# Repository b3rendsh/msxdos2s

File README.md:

# msxdos2s
- Enhanced MSX DOS 2.2 / 2.31 in a 32K ROM package
- Enhanced MSX DOS 1
- Optimized BEER, MALT and SODA IDE interface drivers
- Disk hardware interface designs
- MSX JIO client

## Introduction
This repository contains a re-composition of the MSX DOS 2 disk ROM that can be used as a 32K ROM without a ROM mapper (or 16K ROM for the BEER interface) and includes enhancements for large disks. 

There is also a version of MSX DOS 1 which contains enhancements that are based on the 16K BEER IDE disk ROM that SOLiD created.

And thirdly it includes disk drivers for MSX-DOS 1 and 2 that can be used with the BEER, MALT, SODA and JIO disk interfaces.

All functions of MSX DOS 1 and MSX DOS 2 as originally distributed by ASCII have been retained and should work 100% the same except for the changes that are mentioned below.
The disk ROM works with the original msxdos(2).sys and command(2).com loaded from disk media such as a floppy or IDE disk / compact flash card. 
The disk ROM also works if there are other disk interfaces in the machine and it is compliant with the MSX standards to determine which disk interface will be the master.

## Enhanced MSX DOS IDE disk system

[BEER and SODA ROM package](https://github.com/b3rendsh/msxdos2s/blob/main/rom/beer_and_soda.zip)  
[Source code](dev-32k/)  

Following DOS and driver enhancements are included:
1. Support for large disks with a standard Master Boot Record.
2. Maximum of 4 primary partitions and/or 1 or more extended partitions.
3. Maximum of 8 partitions.
4. Support for FAT16 file systems.
5. Boot drive selection (boot menu).
6. Support for standard DOS 2 or Nextor partitions and disk format.

#### MSX DOS 2 changes
1. Added support for [FAT16 partitions](docs/FAT16%20partitions.txt)
2. Kanji and ROM check ("call dos2memchk" in BASIC) are removed to reduce the size of the ROM.
3. The ROM mapper code is removed and all the code is consolidated in a contiguous 32K ROM space.
4. If the turbo R specific changes are included with the DOS v2.31 option then the ROM still works on older machines.

#### MSX DOS 1 changes
1. Added support for [FAT16 partitions](docs/FAT16%20partitions.txt)
2. Added FAT swapper from SOLiD to support partitions larger than 16MB.

#### Universal IDE driver
The IDE driver is split into a common DOS layer and a low level disk interface layer. It currently supports the BEER-202, BEER-232 and SODA disk interface hardware. If the hardware is not detected then a dummy driver is used.
1. The code is optimized to increase the data transfer rate.
2. Detection of hardware and I/O ports for the MALT and SODA interfaces.
3. Includes support for extended partitions and up to 8 drives.
4. Only one master IDE disk is supported. No master/slave or ATAPI (CDROM) drives. The SODA interface works with CF cards only.
5. Optional execution of boot code in the MBR, in addition or as a replacement for the boot menu.

## Disk interfaces 
**BEER-202 IDE interface**  
This is the original BEER interface, there are several designs with small variations that you can build yourself.  
The [16K MSX-DOS 1 disk ROM](rom/) and [16K MSX-DOS 2 disk ROM](dev-16k/) can be used with this interface.  
  
[**BEER-232 IDE interface**](hardware/beer-232/)  
The BEER-232 cartridge is derived from the BEER-202 and supports 2x 32K disk ROM instead of a single 16K ROM.

[**MALT IDE interface**](hardware/malt/)  
The MALT cartridge is a more robust alternative for the classic BEER IDE that also uses a 8255 PPI chip.

[**SODA IDE interface**](https://github.com/Danjovic/Soda-IDE)  
The SODA IDE cartridge design is based on a RCBus Compact Flash module. Danjovic adapted this design for MSX and made the PCB layout.  
  
[**MSX JIO**](https://github.com/louthrax/MSXJIO)  
Remote serial disk solution from Louthrax. It consists of a disk image server on a PC or android phone, a MSX client and a serial connection over the MSX joystick (gpio) port 2 using a ftdi cable or bluetooth adapter. 

[**MSX JIO CART**](https://github.com/herraa1/msx-jio-cart-v1)  
MSX JIO cartridge from Herraa1. Software based serial communnications like MSXJIO but without using joystick port 2.

[**TASTE program**](https://github.com/b3rendsh/cxland/tree/main/apps/taste)  
IDE disk info and test utility for MSX and RomWBW compatible computers. Works with BEER, MALT and SODA interfaces.

## Older versions

#### 32K MSX DOS 2.2
[ROM binaries](rom/)  
[Source files](mod-32k/)  
The main changes compared to ASCII's MSXDOS 2.2 are that this ROM works without a ROM mapper and doesn't contain Kanji support. Only the original dummy disk driver from ASCII is included, no OEM disk interface driver. Also the enhancements that are mentioned above are not included. 

#### 16K BEER-IDE 2.0
[BEER-IDE 2.0 ROM](https://github.com/b3rendsh/msxdos2s/blob/main/rom/BEER20_DISK.ROM)  
[Source files](mod-beer20/)  
The main improvement compared to the 1.9 driver is that it will work with other disk systems in the machine that have higher DOS versions e.g. a SUNRISE IDE with MSX DOS 2.2 or Nextor. Some other nasty bugs have been fixed. In the source code all the differences between v1.9 and v2.0 are marked and commented in detail.

To use MiSiX DOS use the 2.0 ROM or compile with 1.9 compatibility options, newer ROM versions don't work with MiSiX.

## Contributions
Although contributions of all kinds are welcome, I have no intention to add any more features or modify the DOS kernel in this repository.

Please create an issue if you want to report a bug or have any requests or suggestions. Pull requests from forks are currently not supported.

## License
Most of the sources are a re-composition of the creative work of ASCII and others. They are shared here for educational and non commercial purposes only. It is believed that these works are being used in accordance with the intentions and/or licensing of their creators.

The Creative Commons license terms apply to all custom source code, drivers and binaries.

The material is provided freely and "as it is" in the hope that it will be useful, but without any warranty of any kind, either expressed or implied. Use at own risk!

## References
MSX system sources:  
https://sourceforge.net/projects/msxsyssrc/  
  
MSX DOS 2:  
https://www.msx.org/wiki/MSX-DOS_2  

Other:
- MSX Technical Data Book for MSX-DOS 1
- MSX DOS 2 System Specification 1986-11-26
- Nextor 2.1 Driver Development Guide (github)
- Microsoft FAT Specification (August 30 2005)
- IDE ata3 specification (Revision 6, 26 October 1995)
- Intel 8255A PPI data sheet (August 1991)

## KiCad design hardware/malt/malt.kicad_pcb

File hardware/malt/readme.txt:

MALT IDE
========

MSX 8255 PPI IDE board that is based on the Eurocard Bus DiskIO V3 PPIDE design
for retrocomputers.

It uses the same 8255 PPI chip as the MSX BEER interface but the IDE control
signals are implemented in a more robust way.

Note: see patch document for the pcb version 1.1, these changes will be included 
in the upcoming pcb version 1.2

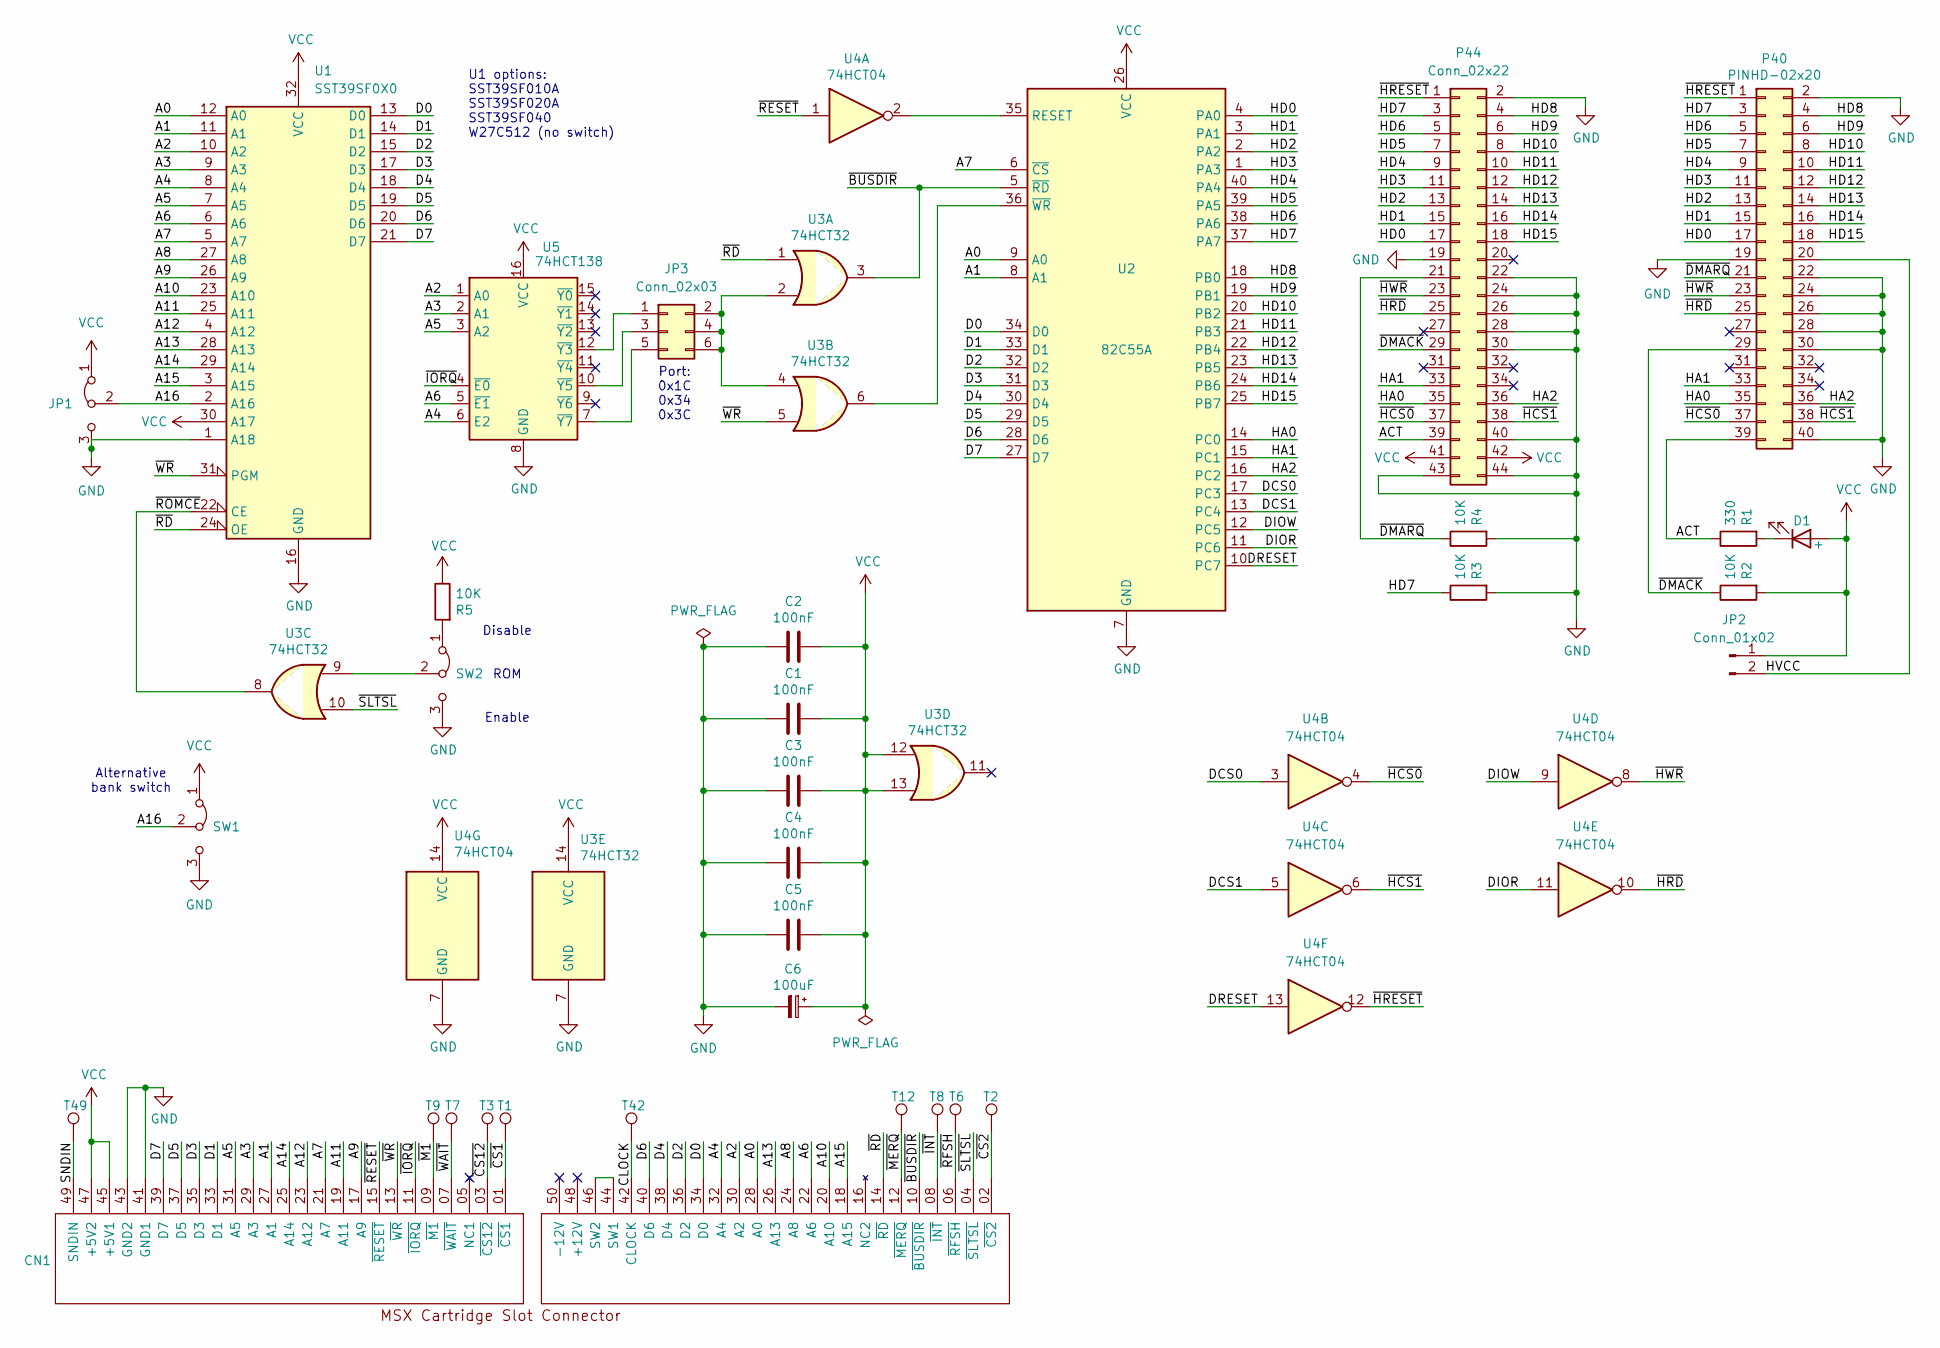
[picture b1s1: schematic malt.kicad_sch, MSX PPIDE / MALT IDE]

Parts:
C1, C2, C3, C4, C5: 100nF; C_Disc_D4.7mm_W2.5mm_P5.00mm
C6: 100uF; CP_lying
CN1: MSX_SLOT_CON; Cart_Konami
D1: +; LED_D3.0mm
JP1: PIN_1x3; PinHeader_1x03_P2.54mm_Vertical
JP2: Conn_01x02; PinHeader_1x02_P2.54mm_Vertical
JP3: Conn_02x03; PinHeader_2x03_P2.54mm_Vertical
P40: PINHD-02x20; PinHeader_2x20_P2.54mm_Horizontal
P44: Conn_02x22; PinHeader_2x22_P2.00mm_Vertical
R1: 330; R_Axial_DIN0204_L3.6mm_D1.6mm_P7.62mm_Horizontal
R2, R3, R4, R5: 10K; R_Axial_DIN0204_L3.6mm_D1.6mm_P7.62mm_Horizontal
SW1, SW2: PIN_1x3; SW_Slide_SPDT_Angled_CK_OS102011MA1Q
T1, T2, T3, T6, T7, T8, T9, T12, T42, T49: TestPoint; SolderWirePad_1x01_SMD_1x2mm
U1: SST39SF0X0; DIP-32_W15.24mm_Socket
U2: 82C55A; DIP-40_W15.24mm
U3: 74HCT32; DIP-14_W7.62mm
U4: 74HCT04; DIP-14_W7.62mm
U5: 74HCT138; DIP-16_W7.62mm

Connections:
/A0: CN1.28 (A0), U1.12 (A0), U2.9 (A0)
/A1: CN1.27 (A1), U1.11 (A1), U2.8 (A1)
/A2: CN1.30 (A2), U1.10 (A2), U5.1 (A0)
/A3: CN1.29 (A3), U1.9 (A3), U5.2 (A1)
/A4: CN1.32 (A4), U1.8 (A4), U5.6 (E2)
/A5: CN1.31 (A5), U1.7 (A5), U5.3 (A2)
/A6: CN1.22 (A6), U1.6 (A6), U5.5 (~E1)
/A7: CN1.21 (A7), U1.5 (A7), U2.6 (~CS)
/A8: CN1.24 (A8), U1.27 (A8)
/A9: CN1.17 (A9), U1.26 (A9)
/A10: CN1.20 (A10), U1.23 (A10)
/A11: CN1.19 (A11), U1.25 (A11)
/A12: CN1.23 (A12), U1.4 (A12)
/A13: CN1.26 (A13), U1.28 (A13)
/A14: CN1.25 (A14), U1.29 (A14)
/A15: CN1.18 (A15), U1.3 (A15)
/A16: JP1.2 (C), SW1.2 (C), U1.2 (A16)
/ACT: P40.39, P44.39, R1.1
/CLOCK: CN1.42 (CLOCK), T42.1
/D0: CN1.34 (D0), U1.13 (D0), U2.34 (D0)
/D1: CN1.33 (D1), U1.14 (D1), U2.33 (D1)
/D2: CN1.36 (D2), U1.15 (D2), U2.32 (D2)
/D3: CN1.35 (D3), U1.17 (D3), U2.31 (D3)
/D4: CN1.38 (D4), U1.18 (D4), U2.30 (D4)
/D5: CN1.37 (D5), U1.19 (D5), U2.29 (D5)
/D6: CN1.40 (D6), U1.20 (D6), U2.28 (D6)
/D7: CN1.39 (D7), U1.21 (D7), U2.27 (D7)
/DCS0: U2.17 (PC3), U4.3
/DCS1: U2.13 (PC4), U4.5
/DIOR: U2.11 (PC6), U4.11
/DIOW: U2.12 (PC5), U4.9
/DRESET: U2.10 (PC7), U4.13
/HA0: P40.35, P44.35, U2.14 (PC0)
/HA1: P40.33, P44.33, U2.15 (PC1)
/HA2: P40.36, P44.36, U2.16 (PC2)
/HD0: P40.17, P44.17, U2.4 (PA0)
/HD1: P40.15, P44.15, U2.3 (PA1)
/HD2: P40.13, P44.13, U2.2 (PA2)
/HD3: P40.11, P44.11, U2.1 (PA3)
/HD4: P40.9, P44.9, U2.40 (PA4)
/HD5: P40.7, P44.7, U2.39 (PA5)
/HD6: P40.5, P44.5, U2.38 (PA6)
/HD7: P40.3, P44.3, R3.1, U2.37 (PA7)
/HD8: P40.4, P44.4, U2.18 (PB0)
/HD9: P40.6, P44.6, U2.19 (PB1)
/HD10: P40.8, P44.8, U2.20 (PB2)
/HD11: P40.10, P44.10, U2.21 (PB3)
/HD12: P40.12, P44.12, U2.22 (PB4)
/HD13: P40.14, P44.14, U2.23 (PB5)
/HD14: P40.16, P44.16, U2.24 (PB6)
/HD15: P40.18, P44.18, U2.25 (PB7)
/HVCC: JP2.2, P40.20
/SNDIN: CN1.49 (SNDIN), T49.1
/~BUSDIR: CN1.10 (~BUSDIR), U2.5 (~RD), U3.3
/~CS1: CN1.01 (~CS1), T1.1
/~CS2: CN1.02 (~CS2), T2.1
/~CS12: CN1.03 (~CS12), T3.1
/~DMACK: P40.29, P44.29, R2.1
/~DMARQ: P40.21, P44.21, R4.1
/~HCS0: P40.37, P44.37, U4.4
/~HCS1: P40.38, P44.38, U4.6
/~HRD: P40.25, P44.25, U4.10
/~HRESET: P40.1, P44.1, U4.12
/~HWR: P40.23, P44.23, U4.8
/~INT: CN1.08 (~INT), T8.1
/~IORQ: CN1.11 (~IORQ), U5.4 (~E0)
/~M1: CN1.09 (~M1), T9.1
/~MERQ: CN1.12 (~MERQ), T12.1
/~RD: CN1.14 (~RD), U1.24 (OE), U3.1
/~RESET: CN1.15 (~RESET), U4.1
/~RFSH: CN1.06 (~RFSH), T6.1
/~ROMCE: U1.22 (CE), U3.8
/~SLTSL: CN1.04 (~SLTSL), U3.10
/~WAIT: CN1.07 (~WAIT), T7.1
/~WR: CN1.13 (~WR), U1.31 (PGM), U3.5
GND: C1.2, C2.2, C3.2, C4.2, C5.2, C6.2, CN1.41 (GND1), CN1.43 (GND2), JP1.3 (B), P40.2, P40.19, P40.22, P40.24, P40.26, P40.28, P40.30, P40.40, P44.2, P44.19, P44.22, P44.24, P44.26, P44.28, P44.30, P44.40, P44.43, P44.44, R3.2, R4.2, SW1.3 (B), SW2.3 (B), U1.1 (A18), U1.16 (GND), U2.7 (GND), U3.7 (GND), U4.7 (GND), U5.8 (GND)
unnamed: CN1.44 (SW1), CN1.46 (SW2)
unnamed: D1.1 (K), R1.2
unnamed: JP3.1, U5.12 (~Y3)
unnamed: JP3.2, JP3.4, JP3.6, U3.2, U3.4
unnamed: JP3.3, U5.10 (~Y5)
unnamed: JP3.5, U5.7 (~Y7)
unnamed: R5.2, SW2.1 (A)
unnamed: SW2.2 (C), U3.9
unnamed: U2.35 (RESET), U4.2
unnamed: U2.36 (~WR), U3.6
VCC: C1.1, C2.1, C3.1, C4.1, C5.1, C6.1, CN1.45 (+5V1), CN1.47 (+5V2), D1.2 (A), JP1.1 (A), JP2.1, P44.41, P44.42, R2.2, R5.1, SW1.1 (A), U1.30 (A17), U1.32 (VCC), U2.26 (VCC), U3.12, U3.13, U3.14 (VCC), U4.14 (VCC), U5.16 (VCC)

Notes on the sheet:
Disable ROM Enable
U1 options: SST39SF010A SST39SF020A SST39SF040 W27C512 (no switch)
Port: 0x1C 0x34 0x3C
Alternative bank switch

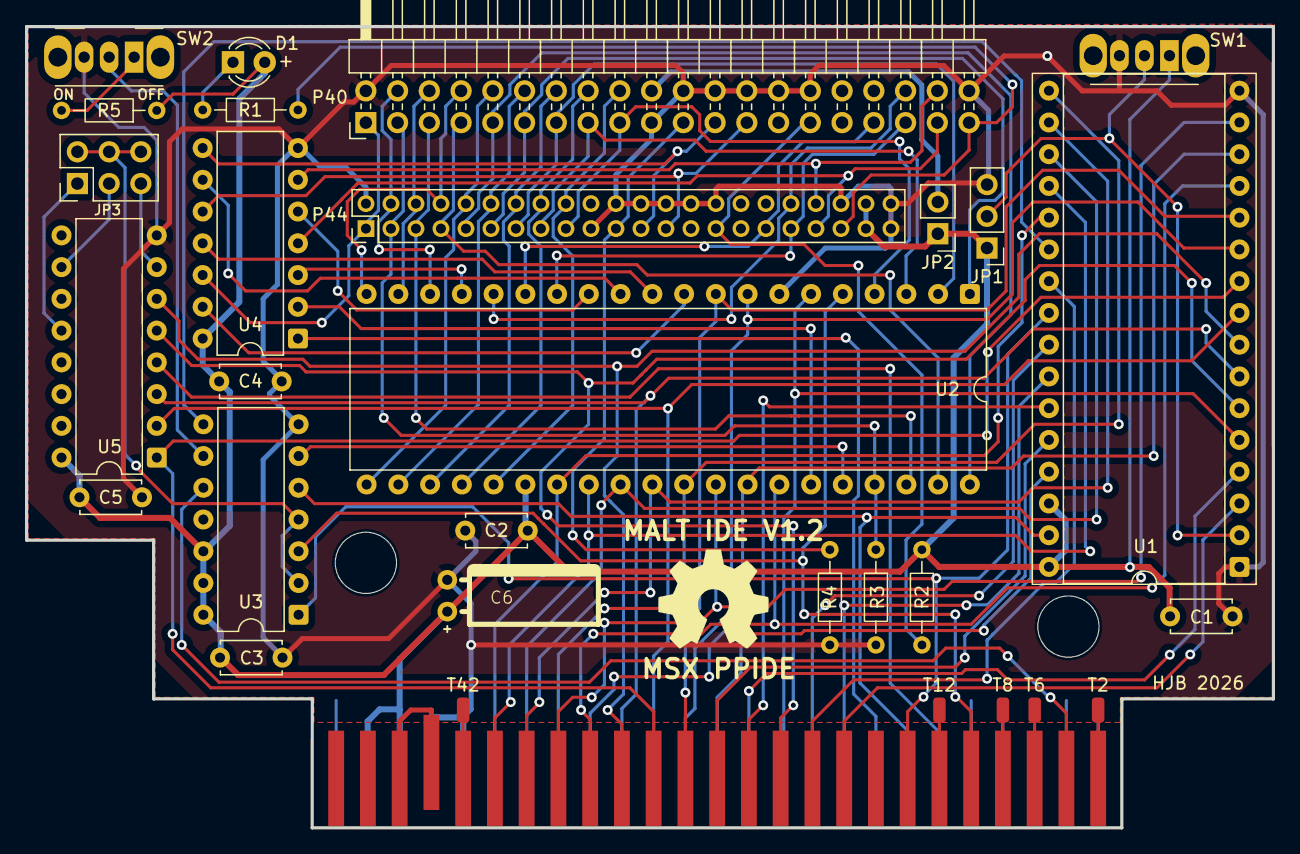
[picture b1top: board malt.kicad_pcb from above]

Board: 2 copper layers, 99.7 x 64.1 mm, 35 parts (0 on the bottom side), 87 nets.

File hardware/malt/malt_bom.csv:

"Id";"Designator";"Footprint";"Quantity","Designation"
1;"C1,C2,C3,C4,C5";"C_Disc_D4.7mm_W2.5mm_P5.00mm";5;"100nF";
2;"C6";"Capacitor electrolytic radial (lying)";1;"100uF";
3;"D1";"LED_D3.0mm";1;"LED Green";
4;"R1";"R_Axial_DIN0204_L3.6mm_D1.6mm_P7.62mm_Horizontal";1;"330";
5;"R2,R3,R4,R5";"R_Axial_DIN0204_L3.6mm_D1.6mm_P7.62mm_Horizontal";3;"10K";
6;"U1";"DIP-32_W15.24mm_Socket";1;"SST39SF010A";
7;"U2";"DIP-40_W15.24mm";1;"82C55A";
8;"U3";"DIP-14_W7.62mm";1;"74HCT32";
9;"U4";"DIP-14_W7.62mm";1;"74HCT04";
10;"U5";"DIP-16_W7.62mm";1;"74HCT138";
11;"P40";"PinHeader_2x20_P2.54mm_Horizontal";1;"PINHD-02x20";
12;"P44";"PinHeader_2x22_P2.00mm_Horizontal";1;"Conn_02x22";
13;"JP1";"PinHeader_1x03_P2.54mm_Vertical";1;"PIN_1x3";
14;"JP2";"PinHeader_1x02_P2.54mm_Vertical";1;"Conn_01x02";
15;"JP3";"PinHeader_2x03_P2.54mm_Vertical";1;"Conn_02x03";
16;"SW1,SW2";"SW_Slide_SPDT_Angled_CK_OS102011MA1Q";1;"PIN_1x3";

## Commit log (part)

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2024-01-23 Initial upload
2024-01-25 Add rom for testing
2024-02-09 Document kernel entry points
    Baselline documentation kernel entry points.
2024-02-15 Experimental beer-ide driver 2.0
    New driver for beer-ide that works with other disk interfaces and DOS 2.2
2024-02-19 Fix boot sector in beer driver
    Fix for DOS format compatibility: don't add hidden sectors value in the boot sector to calculate start of data offset.
2024-02-24 FAT16 patch
    Optional FAT16 patch, no MSX2 check, version info with module suffix, applied default options and character table init routine optimized.
2024-03-05 Update 2.0.1 drive assignment
    To improve compatibility with other DOS versions the drive assignment to internal floppy drives is no longer fixed to A and B.
2024-03-07 32K DOS 2.2 + FAT16 + BEER 2.0
    32K DOS 2.2 sources with beer 2.0 driver integrated and optional FAT16 patch. Initial development version upload.
2024-03-13 2.0.2 Default DPB patch
    DEFAULT DPB patch in the beer 2.0 driver for improved compatibility.
2024-03-19 2.0.3 Drive assignment
    Dynamic drive assignment and use bios to check select key pressed. Resolves phantom drive access issue.
2024-03-22 BEER 2.0 development steps
    Document that describes the process how the beer 2.0 version was created from 1.x sources/binaries.
2024-04-25 BEER232 CART V1.0
    BEER Cartridge with 2x 32K switchable ROM (64K EEPROM) or use as ROM only cartridge for 32K MSXDOS2.
2024-08-28 BEER-232 hardware source
    Added BEER-232 hardware Kicad source files and applicable license.
2024-09-29 2.0.4 FAT16 for partitions > 32MB
    BEER IDE low level DSKIO now compliant with OKEI's FAT16 / Nextor method for 23-bit sector number parameter.
2024-09-29 moved folders and files
    Moved historic files to history folder and moved beer-232 design to subfolder in hardware
2024-10-07 hotfix 2.04a: FAT16 sectornumber
    Hotfix for the BEER driver to support 23-bit sector numbers used in FAT16
2024-10-08 Alternative BEER IDE driver
    WIP: alternative BEER driver with enhanced features
2024-10-10 beer-232 driver update
    Partition type check in BEER-DOS1 and improved performance
2024-10-12 Initial universal IDE driver
    IDE driver with support for BEER PPI 8255 interface and SODA 8-BIT CF IDE interface, works with DOS 1 and 2
2024-10-20 DOS enhancements
    Development update: boot menu, fat16 for dos1, hardware detection,, integrated dummy driver and bugfixes.
2024-10-20 Update Makefile
2024-10-23 2.0.5 root directory entries
    Bugfix to set the root directory entries correctly in the DPB for DOS1
2024-10-24 development update
    Increased performance, added taste utility and cf ide initialization
2024-10-26 ide driver and taste update
    Driver boot message and dynamic IO port probing and selection
2024-10-27 added taste options
    taste beer or taste soda
2024-10-28 soda/taste pictures
2024-10-31 picture - buffer prototype
2024-11-10 update taste, docs and pics
    updated driver source comments and labels, bugfix in taste.com and new pictures
2024-11-12 block read test
    Add block read test to taste.com and revert beer driver to fixed io ports.
2024-11-19 development update
    fat16 optimization, free rom space and format enabled if fat16 option
2024-11-22 development update
    p0 kernel faster disk free space (alloc) for fat16 partitions, removed unused code, labeled routines in source code
2024-11-25 development update
    fat16: if total clusters < 4085 then fat12 else fat16, dskchg dos2 fix for wrong disk error, relabeled page 3 sources and added core_dos2 rom with dummy driver.
2024-12-01 update bootmenu wait time
    Default boot menu wait time set to 3 sec. Value can be changed in patch area at the end of the rom.
2024-12-02 update source comments and labels
2024-12-02 bugfix date and cluster values
    msxdos 2 kernel bugfix use value not address label in date and cluster routines
2024-12-06 ide driver: extended partitions
    identify more than 2 logical drives in an extended partition
2025-01-05 labels
    Update address labels and comments in sources., no binary changes.
2025-02-08 free disk space calculation cut off option
    Add FASTALLOC option for free disk space calculation cut off at 2K clusters for faster DIR command on FAT16 drives, add NODOS1 option to free rom disk space.
2025-02-10 DOS2 boot from FAT16 drive
    Check drives for extended boot signature, continue boot from first (FAT16) drive if no valid bootloader is found in other drives.
2025-02-12 DOS driver update
    Split the ide driver sources in a generic DOS driver file and IDE interface specific driver file. Updated binary download package.
2025-02-15 rom update
    Merged driver DRVINIT and DRVINFO routines and updated the rom binaries
2025-02-23 improved init routines
    improved error handling; free extra rom space for driver (dev)
2025-04-06 kernel code size optimization
    unused buffered output routines removed, bootcode moved from p1 to p0 again so there is more rom space for a larger interface driver.
2025-04-12 jio driver
    changes to prepare for jio driver, work in progress
2025-04-14 jio update
    synced jio driver updates
2025-04-16 add bootcode option
    add option to insert boot code in the mbr, as a replacement or in addition to the bootmenu
2025-04-17 DOS2 GETDPB
    If GETDPB function in DOS 2 is called it can simply return, this reduces driver code size
2025-04-23 JIO + ROM update
    Updated JIO driver with drive to partition mapping on server; updated ROM binaries
2025-04-28 update jio driver
    detect disk change for dos 1 and interrupts disabled during disk i/o
2025-05-12 kernel fixes
    bugfix ramdisk; optimized drive table init for fat16; bugfix . and .. directory entries; added rom16k option
2025-05-12 16K DOS2 rom option
    32K DOS 2 split in 16K ROM and 16K kernel image file loaded from disk, used for testing purposes.
2025-05-12 test instructions
2025-05-18 Added DOS v2.31 / tR rom option
    Use TURBOR directive to include DOS v.231 changes. The rom should also still work on non tR machines. Not all v2.31 features are includes in this rom.
2025-05-19 DOS2 JIO disk change
    DOS2 disk change for JIO driver
2025-05-20 FAT16 disk change
    On FAT16 partitions use the serial number in the Extended BPB to validate same disk in drive for open files..
2025-05-21 update docs / optimization
    FAT16 documentation, apply optmized code
2025-05-21 update FAT16 documentation
2025-05-22 Update JIO driver disk change
    Added disk change logic for disks with multiple drives.
2025-05-29 jio server for test
    Test version of the jio server for linux
2025-06-08 jio server for test
    one file app update from Louthrax date 2025-06-07
2025-06-10 sync ide driver
    sync ide driver sources for alternative dos builds
2025-06-11 sync jio driver
    sync jio driver sources for alternative dos builds
2025-06-14 update binaries
2025-06-16 DOS2 dirtybit + serial
    Set default to only use dirty bit and serial number on DOS2 FAT12 partitions, not on DOS1 or FAT16 to improve performance on very large disks.
2025-06-18 JIO HC-06 Linux instructions
2025-06-19 sync jio
    sync jio sources for release
2025-06-23 JIO protocol specification draft
2025-06-24 update hc-06 linux installation notes
2025-06-30 Update JIO protocol specification
2025-07-21 JIO alt driver test
    JIO alternative driver for LPT port test
2025-07-22 Update JIO alt driver
2025-07-25 update taste and jio driver
    taste basic binary and jio for parallel port
2025-07-28 JIO uart 16550 driver
    JIO driver for use with 16550 uart default base port 0x80, hardware flow control, no fifo buffer, 115K2 with 1.8Mhz clock
2025-07-28 JIO drivers small bugfixes
    DOS 1 driver write sector fix and UART driver receive time-out set rts off
2025-08-04 sync drivers
    Added MAXENT option for DOS 1
2025-08-12 Update IDEDOS1
    FAT16: fast alloc and internal 16-bit directory entries, cosmetic source text changes, extra nternal variables moved to DOS workarea and bugfix FAT swapper
2025-08-12 update rom download package
2025-09-01 jio driver flags
    prevent assembler warning
2025-12-05 jio: add support for jiocart
    This path adds support for the jiocart cartridge.
    See https://github.com/herraa1/msx-jio-cart-v1
2025-12-07 Update JIO driver and add JIOCART support
    See issue #13
2025-12-09 update jio driver
    optimized jio uart interface driver, removed old jio test binaries
2025-12-11 update jio driver, added cart detection
    See issue #13
2025-12-11 Update Makefile
    removed jiocart build options
2025-12-12 Create license
    License terms for custom source code and binaries
2025-12-12 Update README
    Added contributions and license terms
2025-12-15 small changes
2025-12-15 update binaries
    update binaries rev. 2025-12-15
2026-01-03 Bootable msxdos disk image
    Disk image with 16MB system partition and 100MB FAT16 partition
2026-01-03 Update README.md
    Added MiSiX note
2026-02-11 added beer-202 mod instructions and ppi 8255 test
    see also issue #14
2026-02-12 Update t8255.bas
    fixed line endings and eof
2026-02-20 Update README.md
    Added link to MSX JIO CART
2026-02-20 Update BEER 2.05A
    Small patch to keep chip select asserted while reading the disk information. See issue #15
2026-02-20 update taste
    added debug options and CS always asserted
2026-02-21 update taste
    Changed IDE read register sequence
2026-02-22 update taste
    Added test build options, see issue #15
2026-02-23 Update BEER driver
    Improved BEER IDE control signal timings, see issue #15
2026-02-25 Optimized BEER IDE driver control signals
    Default build option BEER_CS uses optimized control signals, comment out in disk.inc to use old control signals if needed. See issue #15
2026-02-28 update taste
    Added write test option. See issue #15
2026-03-03 msx ppide design
    See issue #16
2026-03-09 text changes
    PPIDE=BEER, CFIDE=SODA, (c) 2026, line endings cr+lf
2026-03-12 update Makefile
    improved maintainability
2026-03-16 msx ppide / malt v1.1
    hardware and software sources for the malt ide interface
    see issue #16
2026-03-17 Update IDE driver
    include MALT IDE binaries and source patch
2026-03-21 FLASK flash ROM writer initial version
2026-03-27 Update README.md
    updated text and links for MALT interface and TASTE program
2026-03-27 moved taste program
    old version in history folder, new version in cxland repository
2026-03-28 malt ide hardware build
2026-03-28 update flask
    added support for other JEDEC compatible flash ROM
2026-03-29 malt pcb v1.1 patch
    See issue #16
2026-04-11 update malt pcb v1.1 patches
2026-04-19 malt v1.2
    see issue #16
2026-04-19 malt 1.2 pictures and bom
2026-04-19 malt 1.2 bom update
2026-04-19 Update readme.md
    corrected text formatting and links
2026-04-19 added malt pictures
    cables, psu and design
2026-04-19 Update readme.md
    added sw1 / sw2 caution text
2026-04-27 update malt pcb design picture
